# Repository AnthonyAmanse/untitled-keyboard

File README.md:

# Untitled Keyboard

This is a choc only wireless split keyboard with pro micro compatible sockets. It's inspired by the Sofle, Lily58, Corne, ... keyboards. It has Kailh choc spacings (18 mm x 17 mm). Keycaps I'm using are MBK choc keycaps which has a size of 17.5 x 16.5. I didn't add support for encoder to make it a bit lighter. Pinky columns has a 0.5u vertical offset to make it more comfortable (at least for me). Bottom row has 2 x 1.5u keys with an angle. I thought this would make the thumb cluster more comfortable and reachable. In my experience with this keyboard, the thumb keys are more comfortable when the keyboard is tented. OLED is supported as well - make sure you have a big battery as it consumes a lot of power. I'm using 2000 mAh. This should last me 3-4 weeks based on [ZMK's power profiler](https://zmkfirmware.dev/power-profiler).

The pro micro socket has a bit more width spacing to support the bluemicro840's 20mm width. I've only tested this keyboard with ZMK firmware but it should work for QMK as well since I've put in a slot for the TRRS jacks. Keyboard doesn't have a name so feel free to remove or change the silkscreen on the PCB!

## Build log/guide

1. [Materials](docs/materials.md)
2. [Building the Keyboard](docs/buildguide.md)
3. [Firmware](docs/firmware.md)

## Photos

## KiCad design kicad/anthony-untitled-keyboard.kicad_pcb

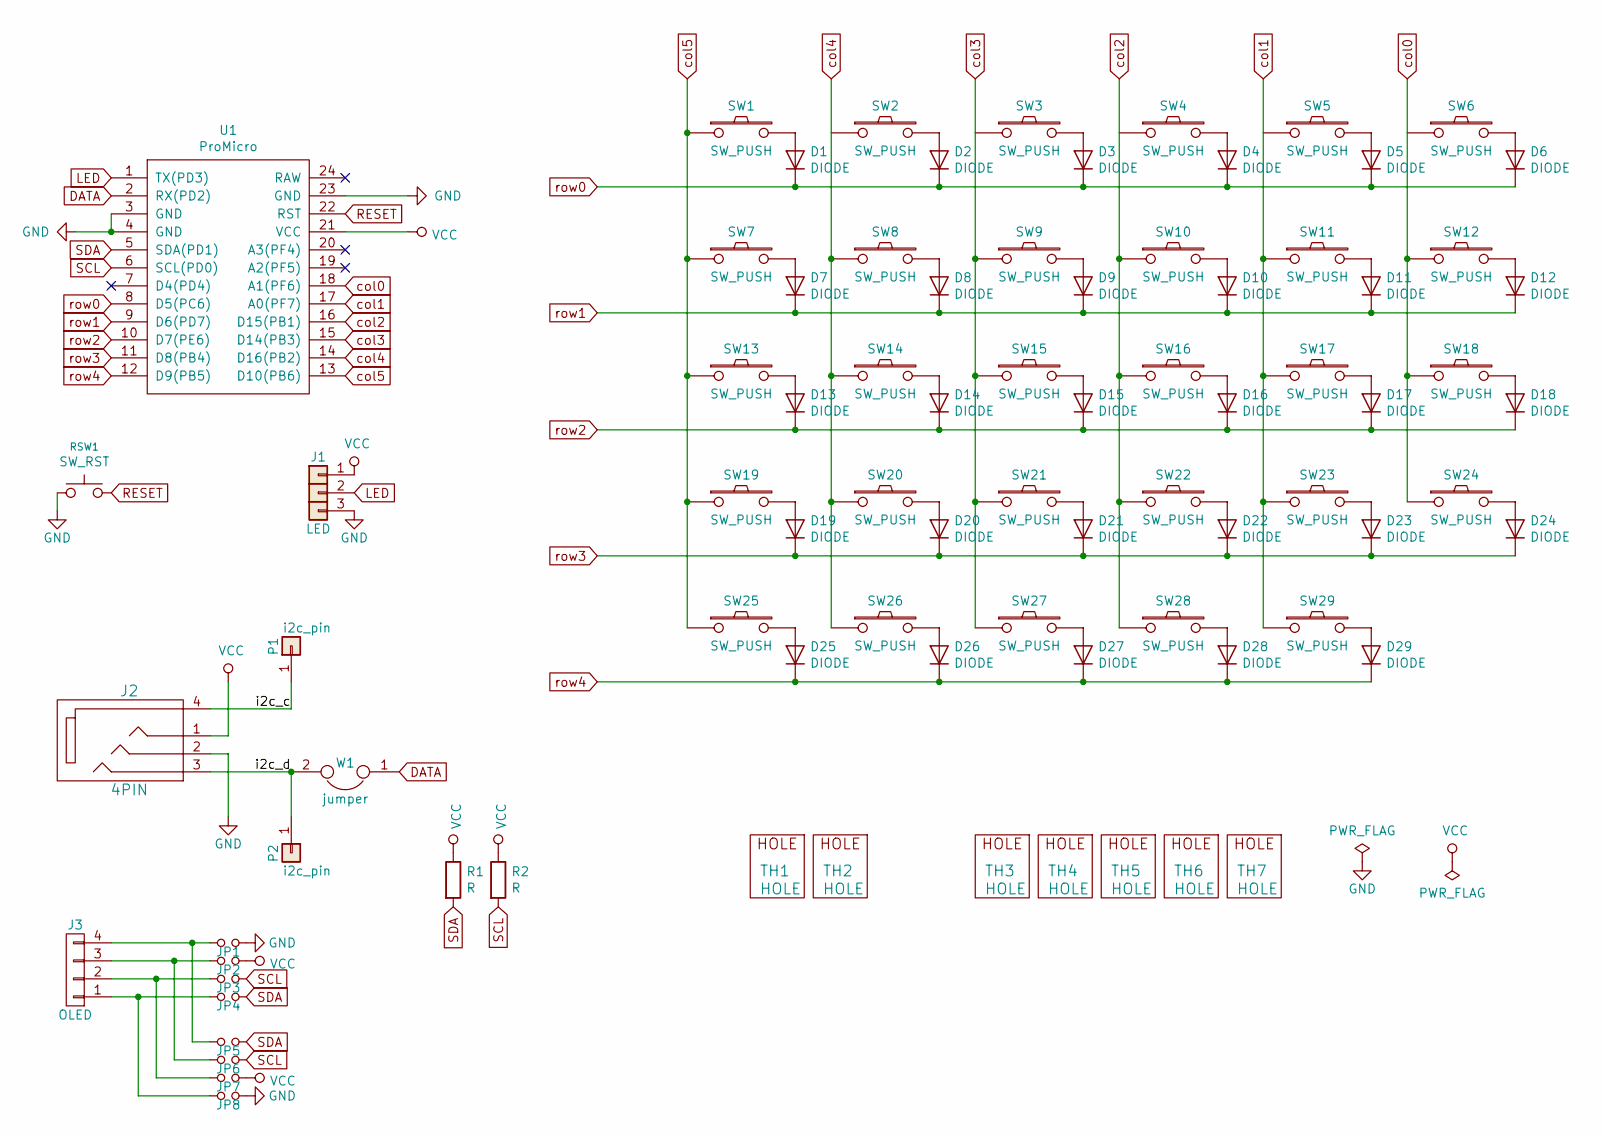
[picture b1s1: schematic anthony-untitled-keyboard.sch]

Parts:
D1, D2, D3, D4, D5, D6, D7, D8, D9, D10, D11, D12, D13, D14, D15, D16, D17, D18, D19, D20, D21, D22, D23, D24, D25, D26, D27, D28, D29: DIODE; Diode_SOD123
J1: LED
J2: 4PIN; MJ-4PP-9
J3: OLED; OLED_4Pin
JP1, JP2, JP3, JP4, JP5, JP6, JP7, JP8: Device_Jumper_NO_Small; Jumper
P1, P2: i2c_pin; 1pin_conn
R1, R2: R; RESISTOR_mini
RSW1: SW_RST; TACT_SWITCH_TVBP06
SW1, SW2, SW3, SW4, SW5, SW6, SW7, SW8, SW9, SW10, SW11, SW12, SW13, SW14, SW15, SW16, SW17, SW18, SW19, SW20, SW21, SW22, SW23, SW24, SW25, SW26, SW27, SW28, SW29: SW_PUSH; Kailh_socket_PG1350_reversible
TH1, TH2: HOLE; M2_HOLE_PCB
TH3, TH4, TH5, TH6, TH7: HOLE; HOLE_M2_TH
U1: ProMicro
W1: jumper; jumper_data

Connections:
/i2c_c: J2.4, P1.1
/i2c_d: J2.3, P2.1, W1.2
DATA: U1.2 (RX(PD2)), W1.1
GND: J1.3, J2.2, JP1.2, JP8.2, RSW1.1, U1.3 (GND), U1.4 (GND), U1.23 (GND)
LED: J1.2, U1.1 (TX(PD3))
unnamed: D1.2 (A), SW1.2
unnamed: D2.2 (A), SW2.2
unnamed: D3.2 (A), SW3.2
unnamed: D4.2 (A), SW4.2
unnamed: D5.2 (A), SW5.2
unnamed: D6.2 (A), SW6.2
unnamed: D7.2 (A), SW7.2
unnamed: D8.2 (A), SW8.2
unnamed: D9.2 (A), SW9.2
unnamed: D10.2 (A), SW10.2
unnamed: D11.2 (A), SW11.2
unnamed: D12.2 (A), SW12.2
unnamed: D13.2 (A), SW13.2
unnamed: D14.2 (A), SW14.2
unnamed: D15.2 (A), SW15.2
unnamed: D16.2 (A), SW16.2
unnamed: D17.2 (A), SW17.2
unnamed: D18.2 (A), SW18.2
unnamed: D19.2 (A), SW19.2
unnamed: D20.2 (A), SW20.2
unnamed: D21.2 (A), SW21.2
unnamed: D22.2 (A), SW22.2
unnamed: D23.2 (A), SW23.2
unnamed: D24.2 (A), SW24.2
unnamed: D25.2 (A), SW25.2
unnamed: D26.2 (A), SW26.2
unnamed: D27.2 (A), SW27.2
unnamed: D28.2 (A), SW28.2
unnamed: D29.2 (A), SW29.2
unnamed: J3.1, JP4.1, JP8.1
unnamed: J3.2, JP3.1, JP7.1
unnamed: J3.3, JP2.1, JP6.1
unnamed: J3.4, JP1.1, JP5.1
RESET: RSW1.2, U1.22 (RST)
SCL: JP3.2, JP6.2, R2.2, U1.6 (SCL(PD0))
SDA: JP4.2, JP5.2, R1.2, U1.5 (SDA(PD1))
VCC: J1.1, J2.1, JP2.2, JP7.2, R1.1, R2.1, U1.21 (VCC)
col0: SW6.1, SW12.1, SW18.1, SW24.1, U1.18 (A1(PF6))
col1: SW5.1, SW11.1, SW17.1, SW23.1, SW29.1, U1.17 (A0(PF7))
col2: SW4.1, SW10.1, SW16.1, SW22.1, SW28.1, U1.16 (D15(PB1))
col3: SW3.1, SW9.1, SW15.1, SW21.1, SW27.1, U1.15 (D14(PB3))
col4: SW2.1, SW8.1, SW14.1, SW20.1, SW26.1, U1.14 (D16(PB2))
col5: SW1.1, SW7.1, SW13.1, SW19.1, SW25.1, U1.13 (D10(PB6))
row0: D1.1 (K), D2.1 (K), D3.1 (K), D4.1 (K), D5.1 (K), D6.1 (K), U1.8 (D5(PC6))
row1: D7.1 (K), D8.1 (K), D9.1 (K), D10.1 (K), D11.1 (K), D12.1 (K), U1.9 (D6(PD7))
row2: D13.1 (K), D14.1 (K), D15.1 (K), D16.1 (K), D17.1 (K), D18.1 (K), U1.10 (D7(PE6))
row3: D19.1 (K), D20.1 (K), D21.1 (K), D22.1 (K), D23.1 (K), D24.1 (K), U1.11 (D8(PB4))
row4: D25.1 (K), D26.1 (K), D27.1 (K), D28.1 (K), D29.1 (K), U1.12 (D9(PB5))

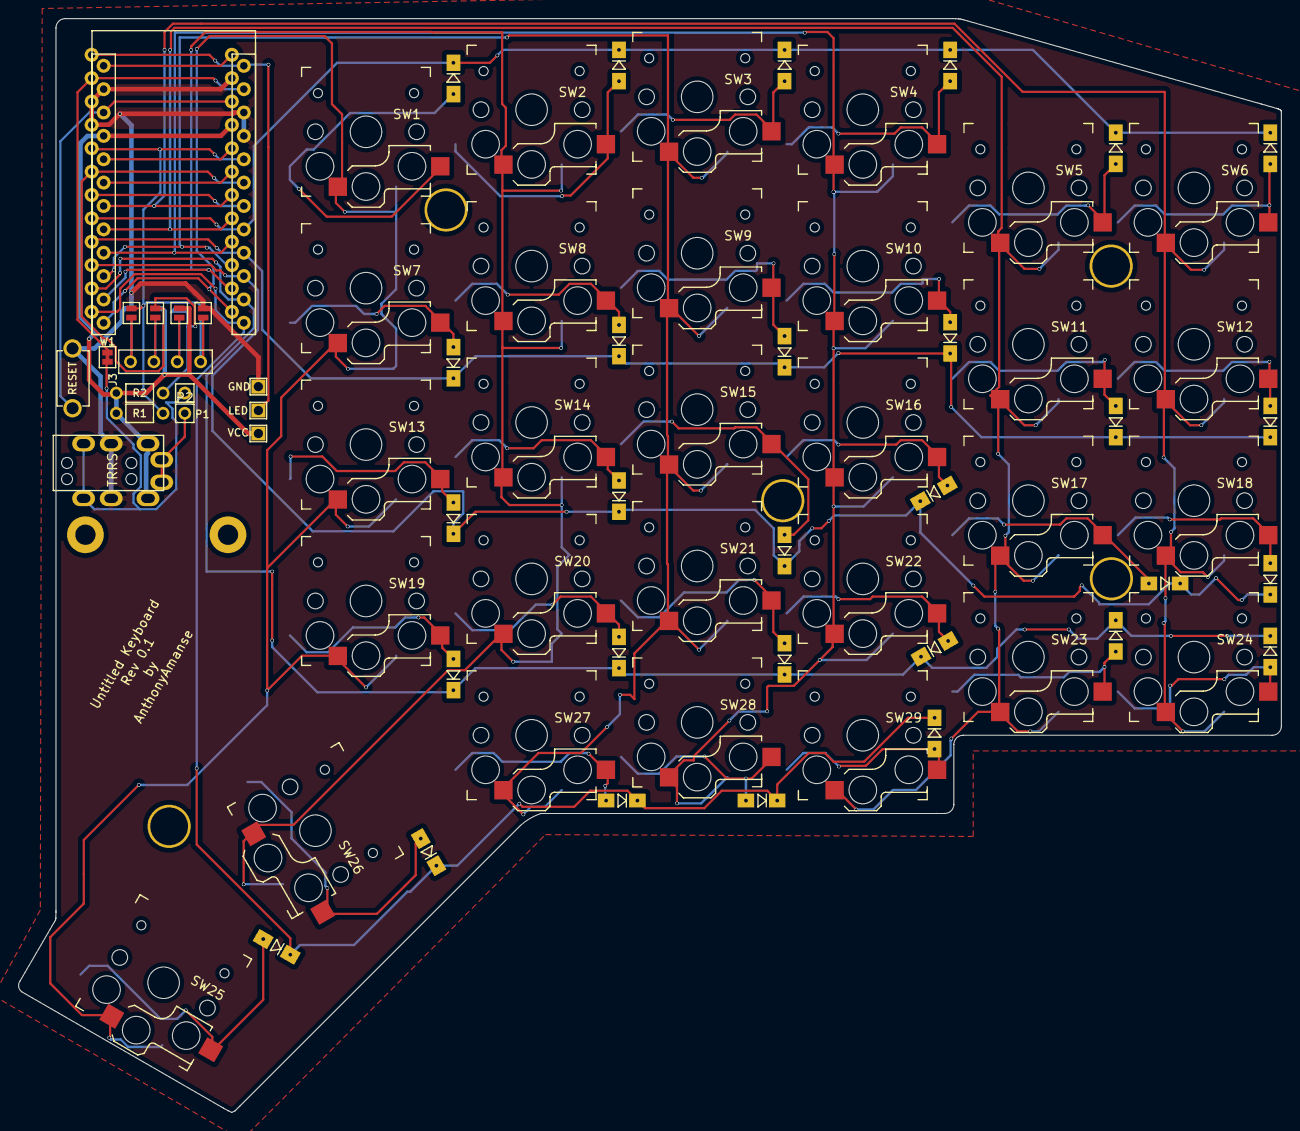
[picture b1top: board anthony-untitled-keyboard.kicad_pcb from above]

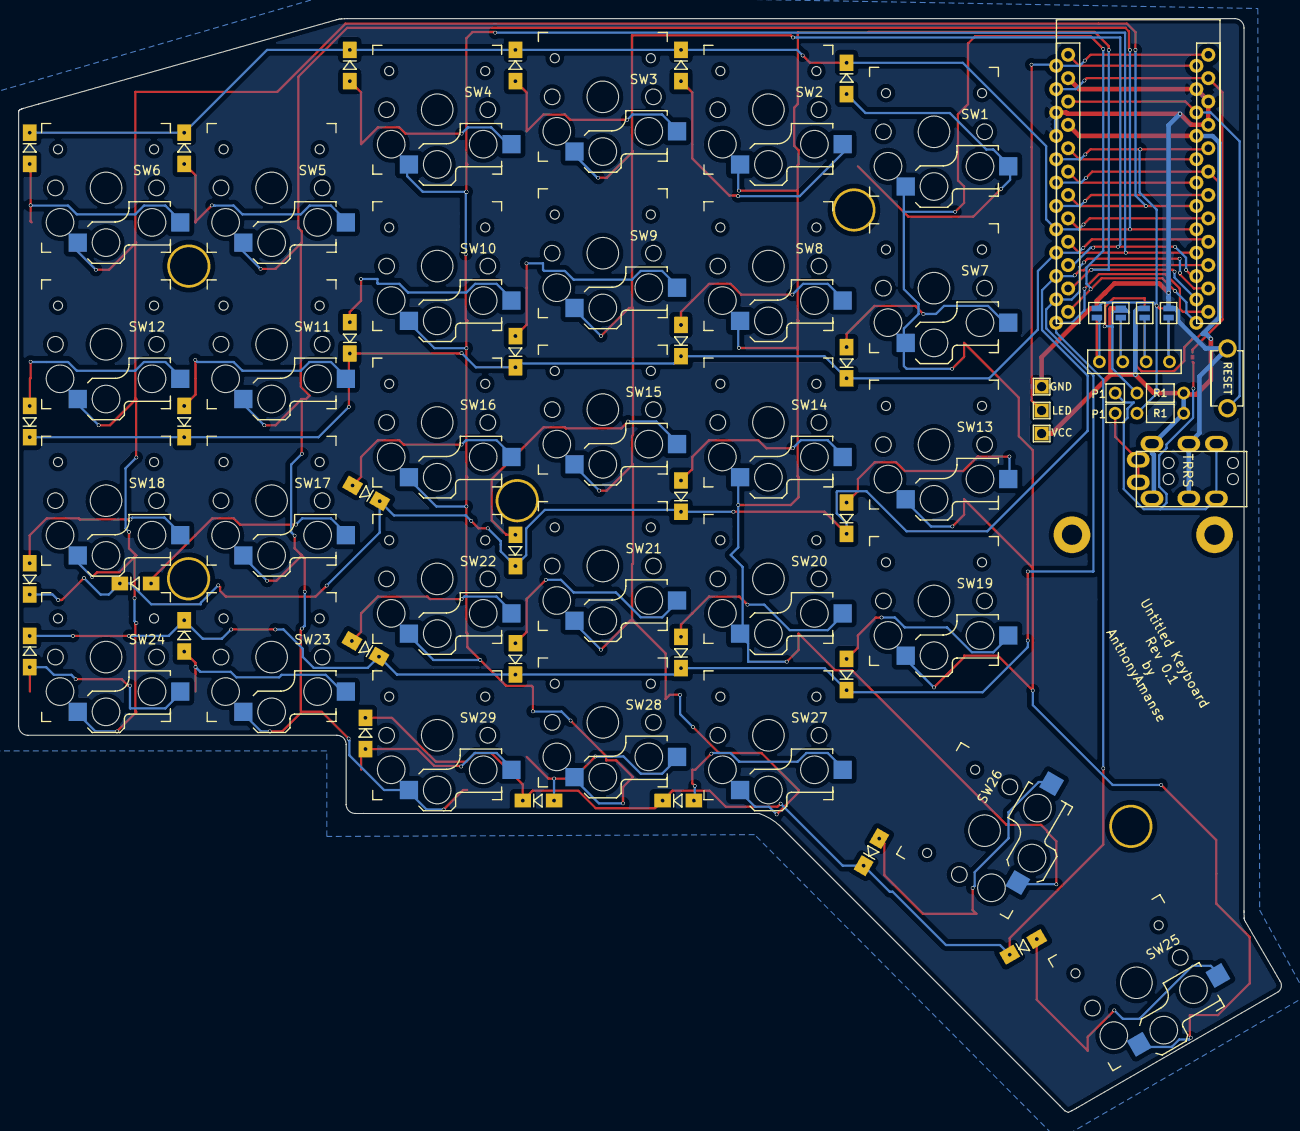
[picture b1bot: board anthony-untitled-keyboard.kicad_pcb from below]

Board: 2 copper layers, 137.3 x 118.9 mm, 83 parts (5 on the bottom side), 53 nets.

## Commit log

2021-05-31 Add gerber files
    This commit adds gerber files for the main pcb, switch plate, and bottom plate.
2021-05-31 Add build log/guide on top of readme
2021-05-31 Fix bom format
